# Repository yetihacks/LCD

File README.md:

LCD adapter 
Copyright 2012 Michael Paholski 
Yetihacks

INSTALLATION The design is saved as an EAGLE project. EAGLE PCB design software is available from www.cadsoftusa.com free for non-commercial use. To use this project download it and place the directory containing these files into the "eagle" directory on your computer. 

DISTRIBUTION The specific terms of distribution of this project are governed by the license referenced below.

LICENSE This work is licensed under the Creative Commons Attribution-Share Alike License. To view a copy of this license, visit

http://creativecommons.org/licenses/by-sa/3.0/ http://creativecommons.org/licenses/by-sa/3.0/legalcode

or send a letter to

Creative Commons 171 Second Street, Suite 300 San Francisco California, 94105 USA

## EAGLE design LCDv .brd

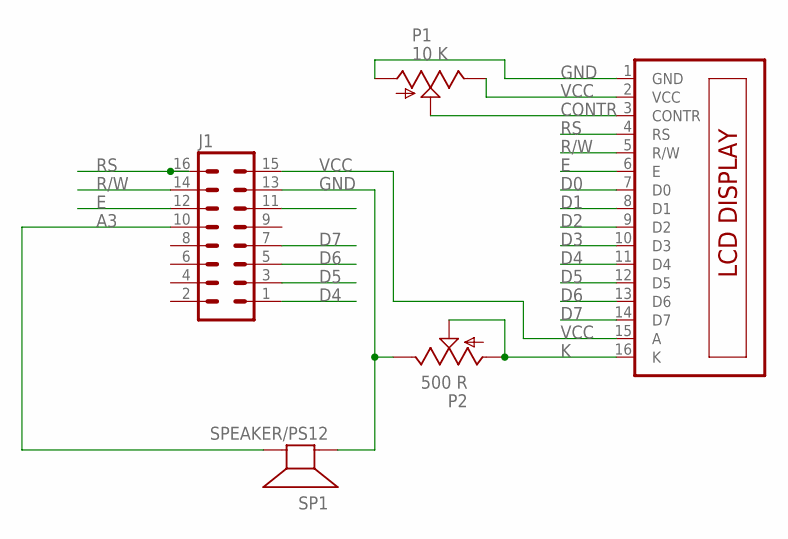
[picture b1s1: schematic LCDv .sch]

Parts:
J1: ML16L
LCD1: DISP_LCD-4X20; DISP_LCD_4X20
P1: 10 K; 6MM
P2: 500 R; 6MM
SP1: SPEAKER/PS12; PS12

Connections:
A3: J1.10, SP1.P$2 (-)
CONTR: LCD1.3 (CONTR), P1.S
D0: LCD1.7 (D0)
D1: LCD1.8 (D1)
D2: LCD1.9 (D2)
D3: LCD1.10 (D3)
D4: J1.1, LCD1.11 (D4)
D5: J1.3, LCD1.12 (D5)
D6: J1.5, LCD1.13 (D6)
D7: J1.7, LCD1.14 (D7)
E: J1.12, LCD1.6 (E)
GND: J1.13, LCD1.1 (GND), P1.A, P2.E, SP1.P$1 (+)
K: LCD1.16 (K), P2.A, P2.S
R/W: J1.14, LCD1.5 (R/W)
RS: J1.16, LCD1.4 (RS)
VCC: J1.15, LCD1.2 (VCC), LCD1.15 (A), P1.E

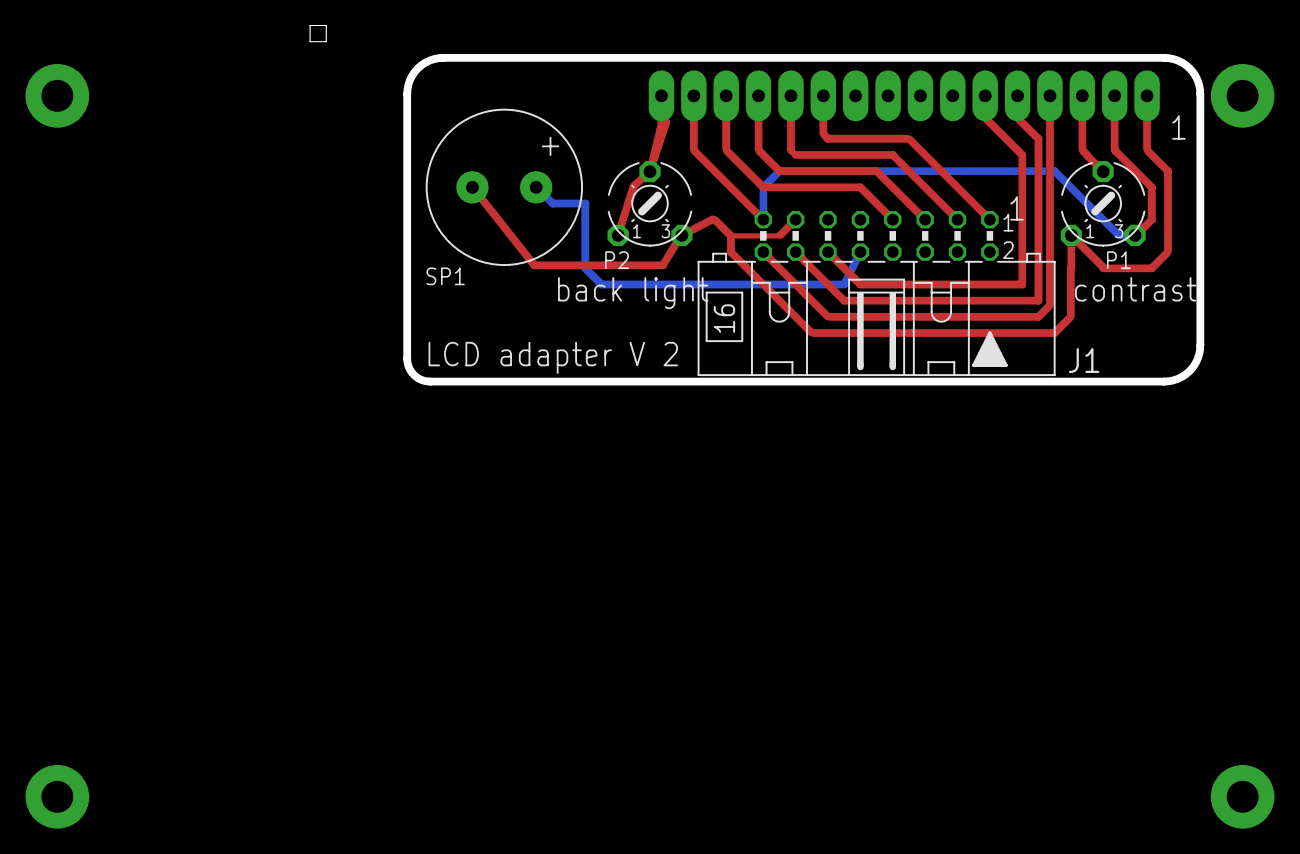
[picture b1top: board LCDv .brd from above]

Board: 2 copper layers, 62.2 x 25.4 mm, 5 parts (1 on the bottom side), 12 nets.

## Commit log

2013-03-10 version 1
